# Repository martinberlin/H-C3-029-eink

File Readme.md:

### nRF52840 mini Badger PCB

This PCB design is based on [this nRF52 module datasheet](https://jlcpcb.com/api/file/downloadByFileSystemAccessId/8612736116701077504)

> E73 - 2 G4 M0 8 S1C are wireless Bluetooth modules designed by
Chengdu Ebyte which feature small size, low power consumption. It
adopt the originally imported RFIC nRF52840 of NORDIC, supporting BLE 4. 2 and BLE 5. 0 . The chip has high- performance ARM CORTEX- M4 F kernel and other peripheral resources, such as
UART, I2C, SPI, ADC, DMA, PWM etc.

The most important goals that this PCB achieves:

 - Very low power consumption. In factors of 2 digits micro-amperes (uA) per minute
 - Simple user interface with a multi-directional switch (up, down, select)
 - All open source, including the BLE sending program (MacOS /iOS)
 - Very simple design and schematics
 - QWIIC connector so can support external I2C sensors (Consumption limit: 200mA, limited by LDO MCP1700-330) 

### PCB 3D Render

### Related repositories

[MFR Badge](https://github.com/bitbank2/MFRBadge) MacOS/iOS app to program the Maker Faire Rome badges

[bb_epaper](https://github.com/bitbank2/bb_epaper) Larry Bank library for SPI epaper displays

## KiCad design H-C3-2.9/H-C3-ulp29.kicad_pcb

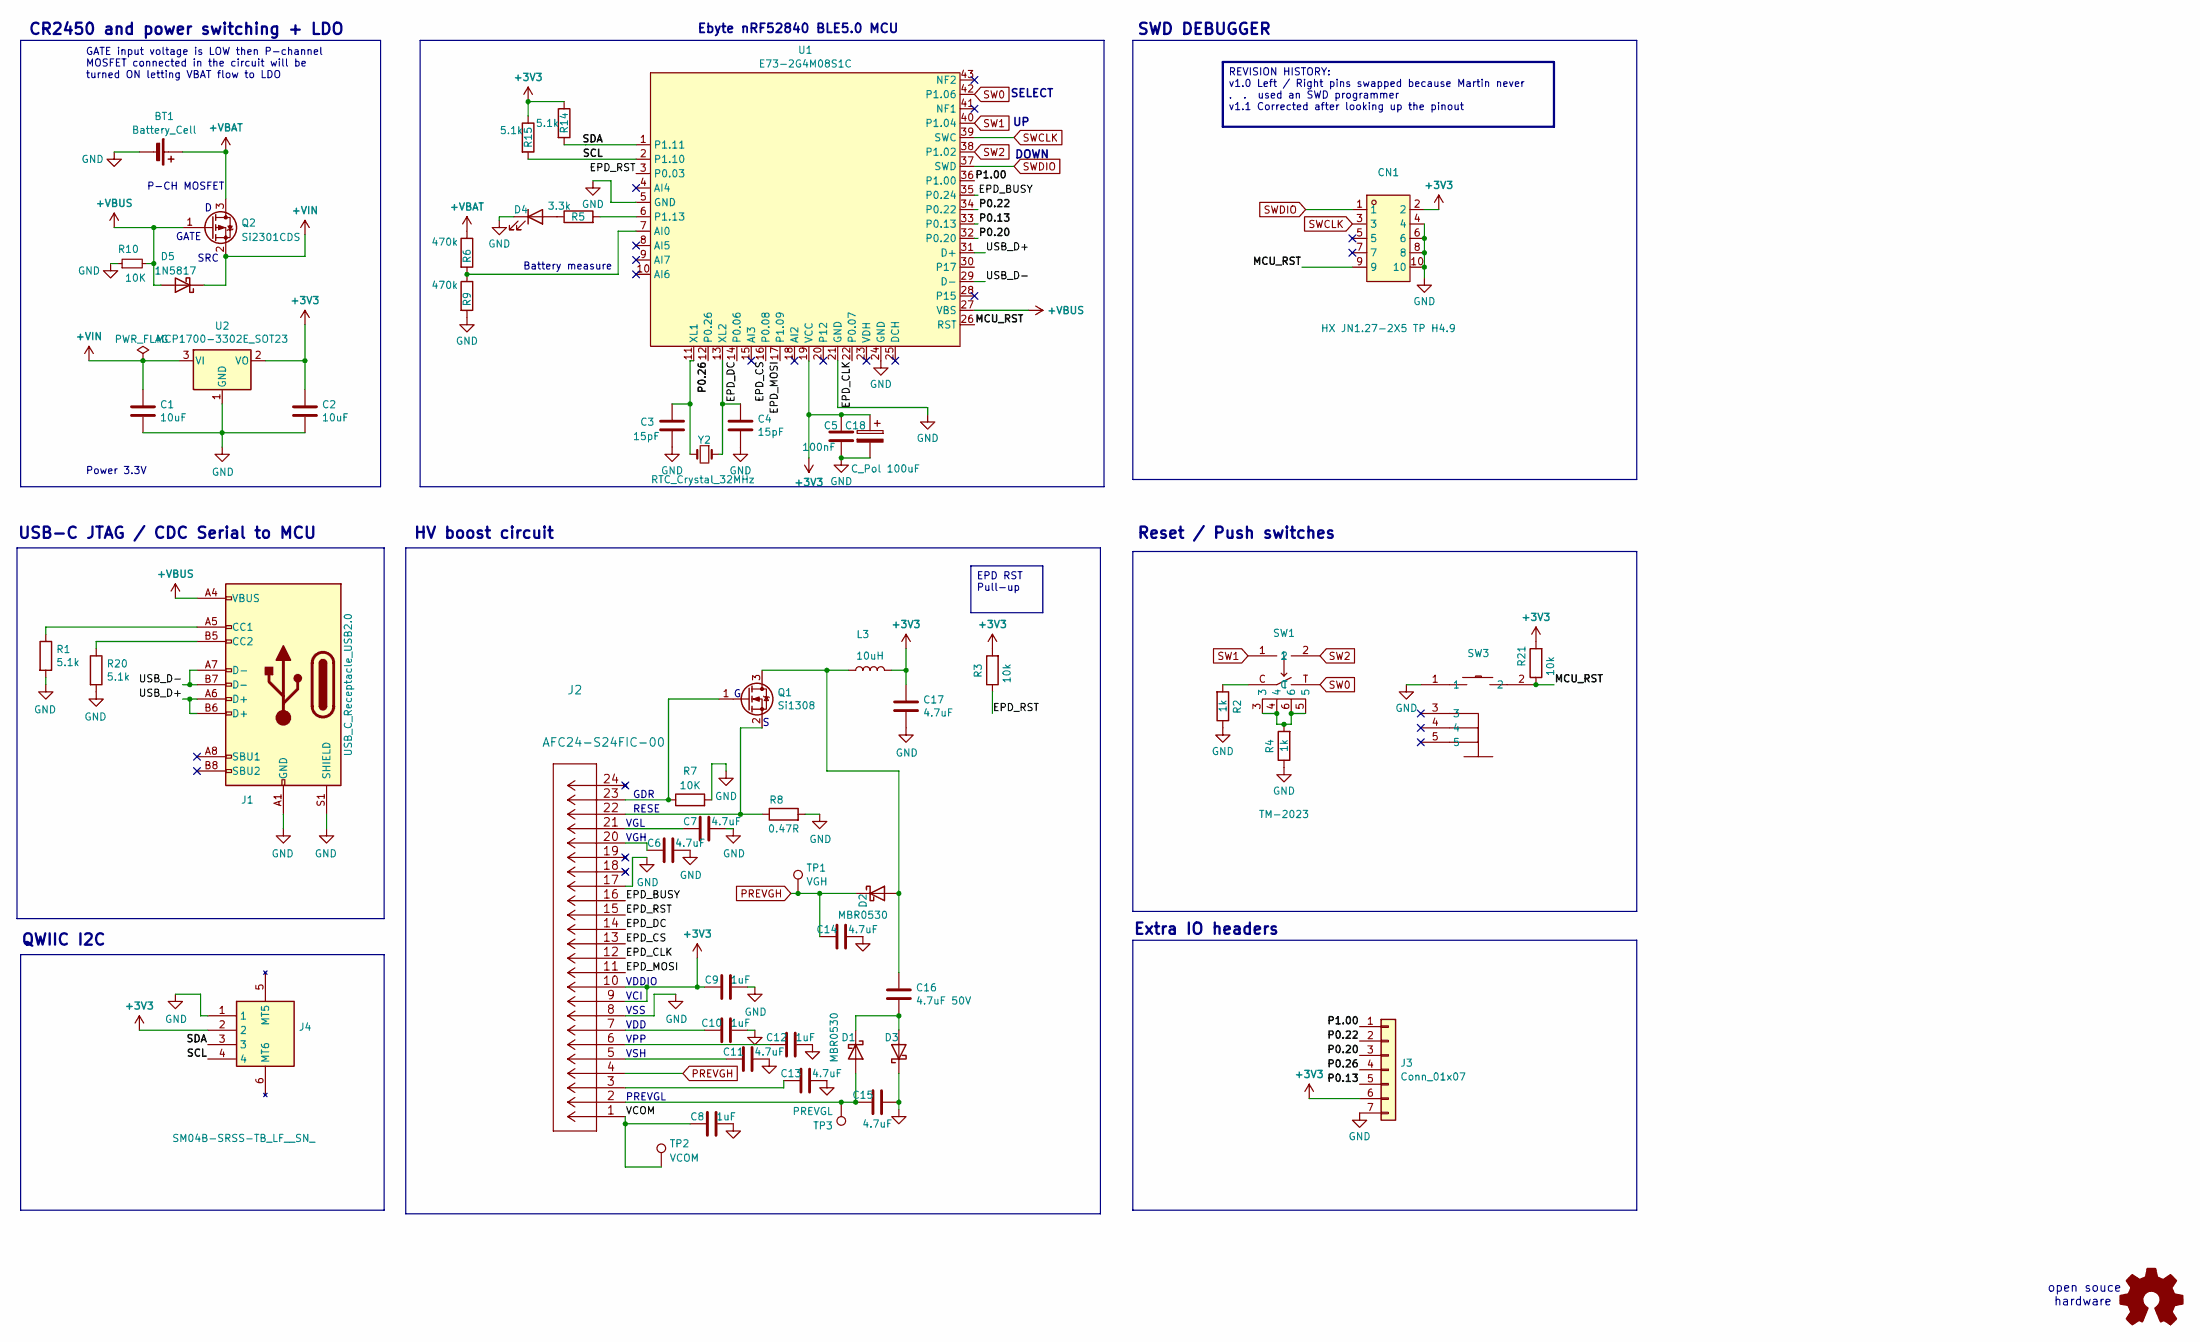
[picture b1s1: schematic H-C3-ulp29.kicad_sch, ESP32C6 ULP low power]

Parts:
BT1: Battery_Cell; BAT-SMD_BS-24-B4AA016; LCSC C964809
C1, C2: 10uF; C_0805_2012Metric; LCSC C15850
C3, C4: 15pF; C_0402_1005Metric; LCSC C32949
C5: 100nF; C_0402_1005Metric; LCSC C1525
C6, C7, C11, C13, C14, C15: 4.7uF; C_0805_2012Metric_Pad1.18x1.45mm_HandSolder; LCSC C1779
C8, C9, C10, C12: 1uF; C_0805_2012Metric_Pad1.18x1.45mm_HandSolder; LCSC C28323
C16: 4.7uF 50V; C_0805_2012Metric_Pad1.18x1.45mm_HandSolder; LCSC C1779
C17: 4.7uF; C_0603_1608Metric; LCSC C19666
C18: C_Pol 100uF; C7171_CAP; LCSC C7171
CN1: HX JN1.27-2X5 TP H4.9; C42372555-SWD_10P-P1.27; LCSC C42372555
D1, D2, D3: MBR0530; D_SOD-123; LCSC C77336
D4: LED; LED_0402_1005Metric; LCSC C131223
D5: 1N5817; D_SOD-123; LCSC C8598
J1: USB_C_Receptacle_USB2.0; USB_C_Receptacle_HRO_TYPE-C-31-M-12; LCSC C165948
J2: AFC24-S24FIC-00; LCSC C262292
J3: Conn_01x07; PinHeader_1x07_P2.54mm_Vertical
J4: SM04B-SRSS-TB_LF__SN_; QWIIC_SM04B-SRSS-TB_LFSN_; Manufacturer_Part_Number SM04B-SRSS-TB(LF)(SN); LCSC C160404
L3: 10uH; SWPA4030S1R0NT; LCSC C38117
Q1: Si1308; SOT-323_SC-70; LCSC C469327
Q2: Si2301CDS; SOT-23; LCSC C10487
R1, R14, R15, R20: 5.1k; R_0603_1608Metric; LCSC C23186
R2, R4: 1k; R_0402_1005Metric; LCSC C11702
R3, R21: 10k; R_0402_1005Metric; LCSC C25744
R5: 3.3k; R_0402_1005Metric; LCSC C25890
R6, R9: 470k; R_0402_1005Metric; LCSC C22369547
R7, R10: 10K; R_0402_1005Metric; LCSC C25744
R8: 0.47R; R_0603_1608Metric; LCSC C103895
SW1: TM-2023; C318951_TM-2023-1; LCSC C318951
SW3: K2-1806SQ-A2DW-04; KEY-SMD_K2-1806SQ-A3DW-04; LCSC C19100323
TP1: VGH; TestPoint_Pad_D1.5mm
TP2: VCOM; TestPoint_Pad_D1.5mm
TP3: PREVGL; TestPoint_Pad_D1.5mm
U1: E73-2G4M08S1C; C356849-nRF52840; LCSC C356849
U2: MCP1700-3302E_SOT23; SOT-23; LCSC C39051
Y2: RTC_Crystal_32MHz; Q13FC1350000400-Crystal; LCSC C32346

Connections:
+3V3: C2.2, C5.2, C9.2, C17.2, C18.1, CN1.2, J2.9, J2.10, J3.6, J4.2, L3.2, R3.2, R14.1, R15.1, R21.2, U1.19 (VCC), U2.2 (VO)
+VBAT: BT1.1 (+), Q2.3 (D), R6.1
+VBUS: D5.2 (A), J1.A4 (VBUS), J1.A9 (VBUS), J1.B4 (VBUS), J1.B9 (VBUS), Q2.1 (G), R10.2, U1.27 (VBS)
+VIN: C1.2, D5.1 (K), Q2.2 (S), U2.3 (VI)
/EPD_BUSY: J2.16, U1.35 (P0.24)
/EPD_CLK: J2.12, U1.22 (P0.07)
/EPD_CS: J2.13, U1.16 (P0.08)
/EPD_DC: J2.14, U1.14 (P0.06)
/EPD_MOSI: J2.11, U1.17 (P1.09)
/EPD_RST: J2.15, R3.1, U1.3 (P0.03)
/MCU_RST: CN1.9, R21.1, SW3.2, U1.26 (RST)
/P0.13: J3.5, U1.33 (P0.13)
/P0.20: J3.3, U1.32 (P0.20)
/P0.22: J3.2, U1.34 (P0.22)
/P0.26: J3.4, U1.12 (P0.26)
/P1.00: J3.1, U1.36 (P1.00)
/SCL: J4.4, R15.2, U1.2 (P1.10)
/SDA: J4.3, R14.2, U1.1 (P1.11)
/USB_D+: J1.A6 (D+), J1.B6 (D+), U1.31 (D+)
/USB_D-: J1.A7 (D-), J1.B7 (D-), U1.29 (D-)
/VCOM: C8.2, J2.1, TP2.1
GND: BT1.2 (-), C1.1, C2.1, C3.1, C4.1, C5.1, C6.1, C7.1, C8.1, C9.1, C10.1, C11.1, C12.1, C13.1, C14.1, C15.1, C17.1, C18.2, CN1.4, CN1.6, CN1.8, CN1.10, D3.1 (K), D4.1 (K), J1.A1 (GND), J1.A12 (GND), J1.B1 (GND), J1.B12 (GND), J1.S1 (SHIELD), J2.8, J2.17, J3.7, J4.1, R1.2, R2.1, R4.1, R7.2, R8.2, R9.2, R10.1, R20.2, SW3.1, U1.5 (GND), U1.21 (GND), U1.24 (GND), U2.1 (GND)
unnamed: C6.2, J2.20
unnamed: C7.2, J2.21
unnamed: C10.2, J2.7
unnamed: C11.2, J2.5
unnamed: C12.2, J2.6
unnamed: C13.2, J2.3
unnamed: C15.2, D1.2 (A), J2.2, TP3.1
unnamed: C16.1, D1.1 (K), D3.2 (A)
unnamed: C16.2, D2.2 (A), L3.1, Q1.3 (D)
unnamed: D4.2 (A), R5.1
unnamed: J1.A5 (CC1), R1.1
unnamed: J1.B5 (CC2), R20.1
unnamed: J2.23, Q1.1 (G), R7.1
unnamed: J2.22, Q1.2 (S), R8.1
unnamed: R2.2, SW1.C
unnamed: R4.2, SW1.3, SW1.4, SW1.5, SW1.6
unnamed: R6.2, R9.1, U1.7 (AI0)
unnamed: R5.2, U1.6 (P1.13)
unnamed: C3.2, U1.11 (XL1), Y2.2
unnamed: C4.2, U1.13 (XL2), Y2.1
PREVGH: C14.2, D2.1 (K), J2.4, TP1.1
SW0: SW1.T, U1.42 (P1.06)
SW1: SW1.1, U1.40 (P1.04)
SW2: SW1.2, U1.38 (P1.02)
SWCLK: CN1.3, U1.39 (SWC)
SWDIO: CN1.1, U1.37 (SWD)

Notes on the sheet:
USB-C JTAG / CDC Serial to MCU
Power 3.3V
Ebyte nRF52840 BLE5.0 MCU
VGH
RESE
VGL
HV boost circuit
VSH
VPP
QWIIC I2C
SRC
GATE
Extra IO headers
open souce hardware
GDR
SELECT
P-CH MOSFET
Battery measure
DOWN
Reset / Push switches
VDDIO
GATE input voltage is LOW then P-channel MOSFET connected in the circuit will be turned ON letting VBAT flow to LDO
SWD DEBUGGER
PREVGL
VSS
VCI
CR2450 and power switching + LDO
VDD
REVISION HISTORY: v1.0 Left / Right pins swapped because Martin never . . used an SWD programmer v1.1 Corrected after looking up the pinout
EPD RST Pull-up

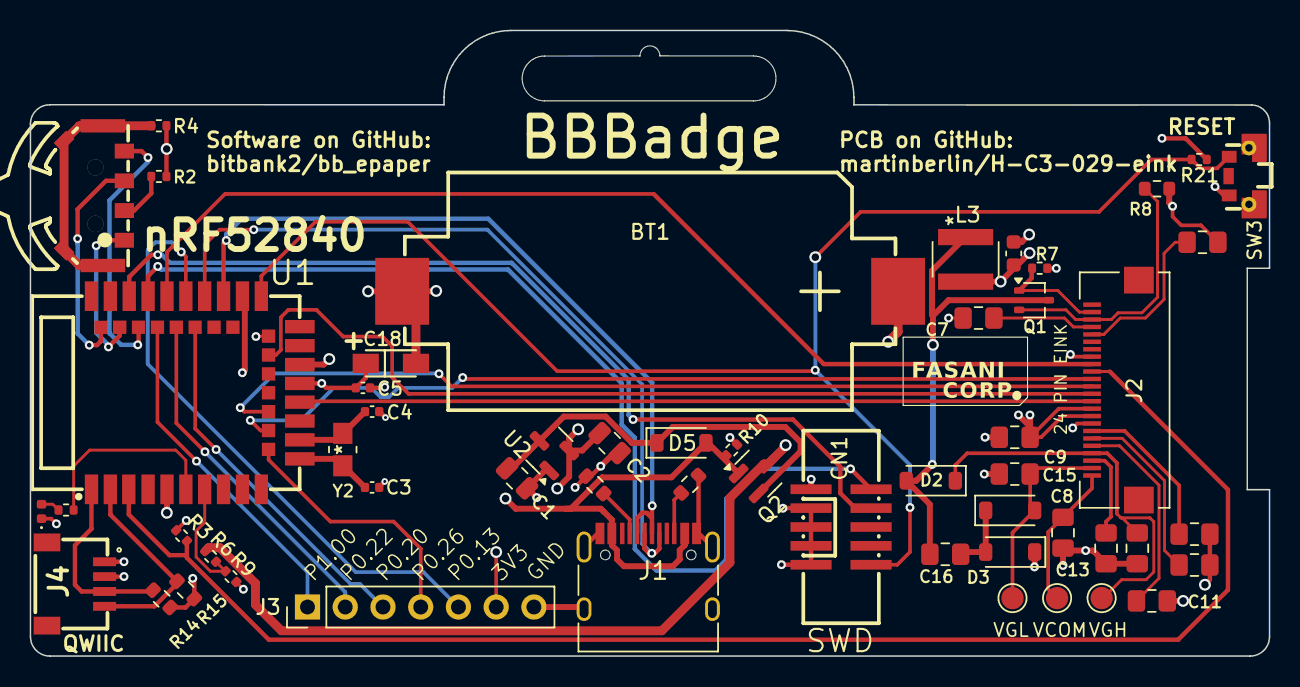
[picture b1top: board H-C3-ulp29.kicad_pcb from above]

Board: 4 copper layers, 83.4 x 42.1 mm, 54 parts (0 on the bottom side), 48 nets.

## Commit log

2025-08-07 Initial commit, unfinished board
2025-08-07 Add PCF RTC
2025-08-08 Layout 1.0
2025-08-08 Schematics updated. All parts on board
2025-08-08 Going forward
2025-08-08 Final decision about MCU
2025-08-09 Starting to test routing posibilities
2025-08-09 Please approve routing
2025-08-09 Add nRF52 RTC crystal
2025-08-09 Placing new knob
2025-08-09 RTC is out, use internal one
2025-08-09 1.0 schematics needs last feedback
2025-08-09 Pre-release please check routing
2025-08-10 FAB attempt 1
2025-08-10 Modified front silkscreen info
2025-08-29 Updated for 1.1
2025-08-29 Last corrections after KiCad updated (was done already for 1.0)
2025-09-26 Add PCB Preview
2025-09-26 Add relevant links
2025-09-26 Add main goals

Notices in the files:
parts and their libraries:
Copyright 2021 Accelerated Designs. All rights reserved.
